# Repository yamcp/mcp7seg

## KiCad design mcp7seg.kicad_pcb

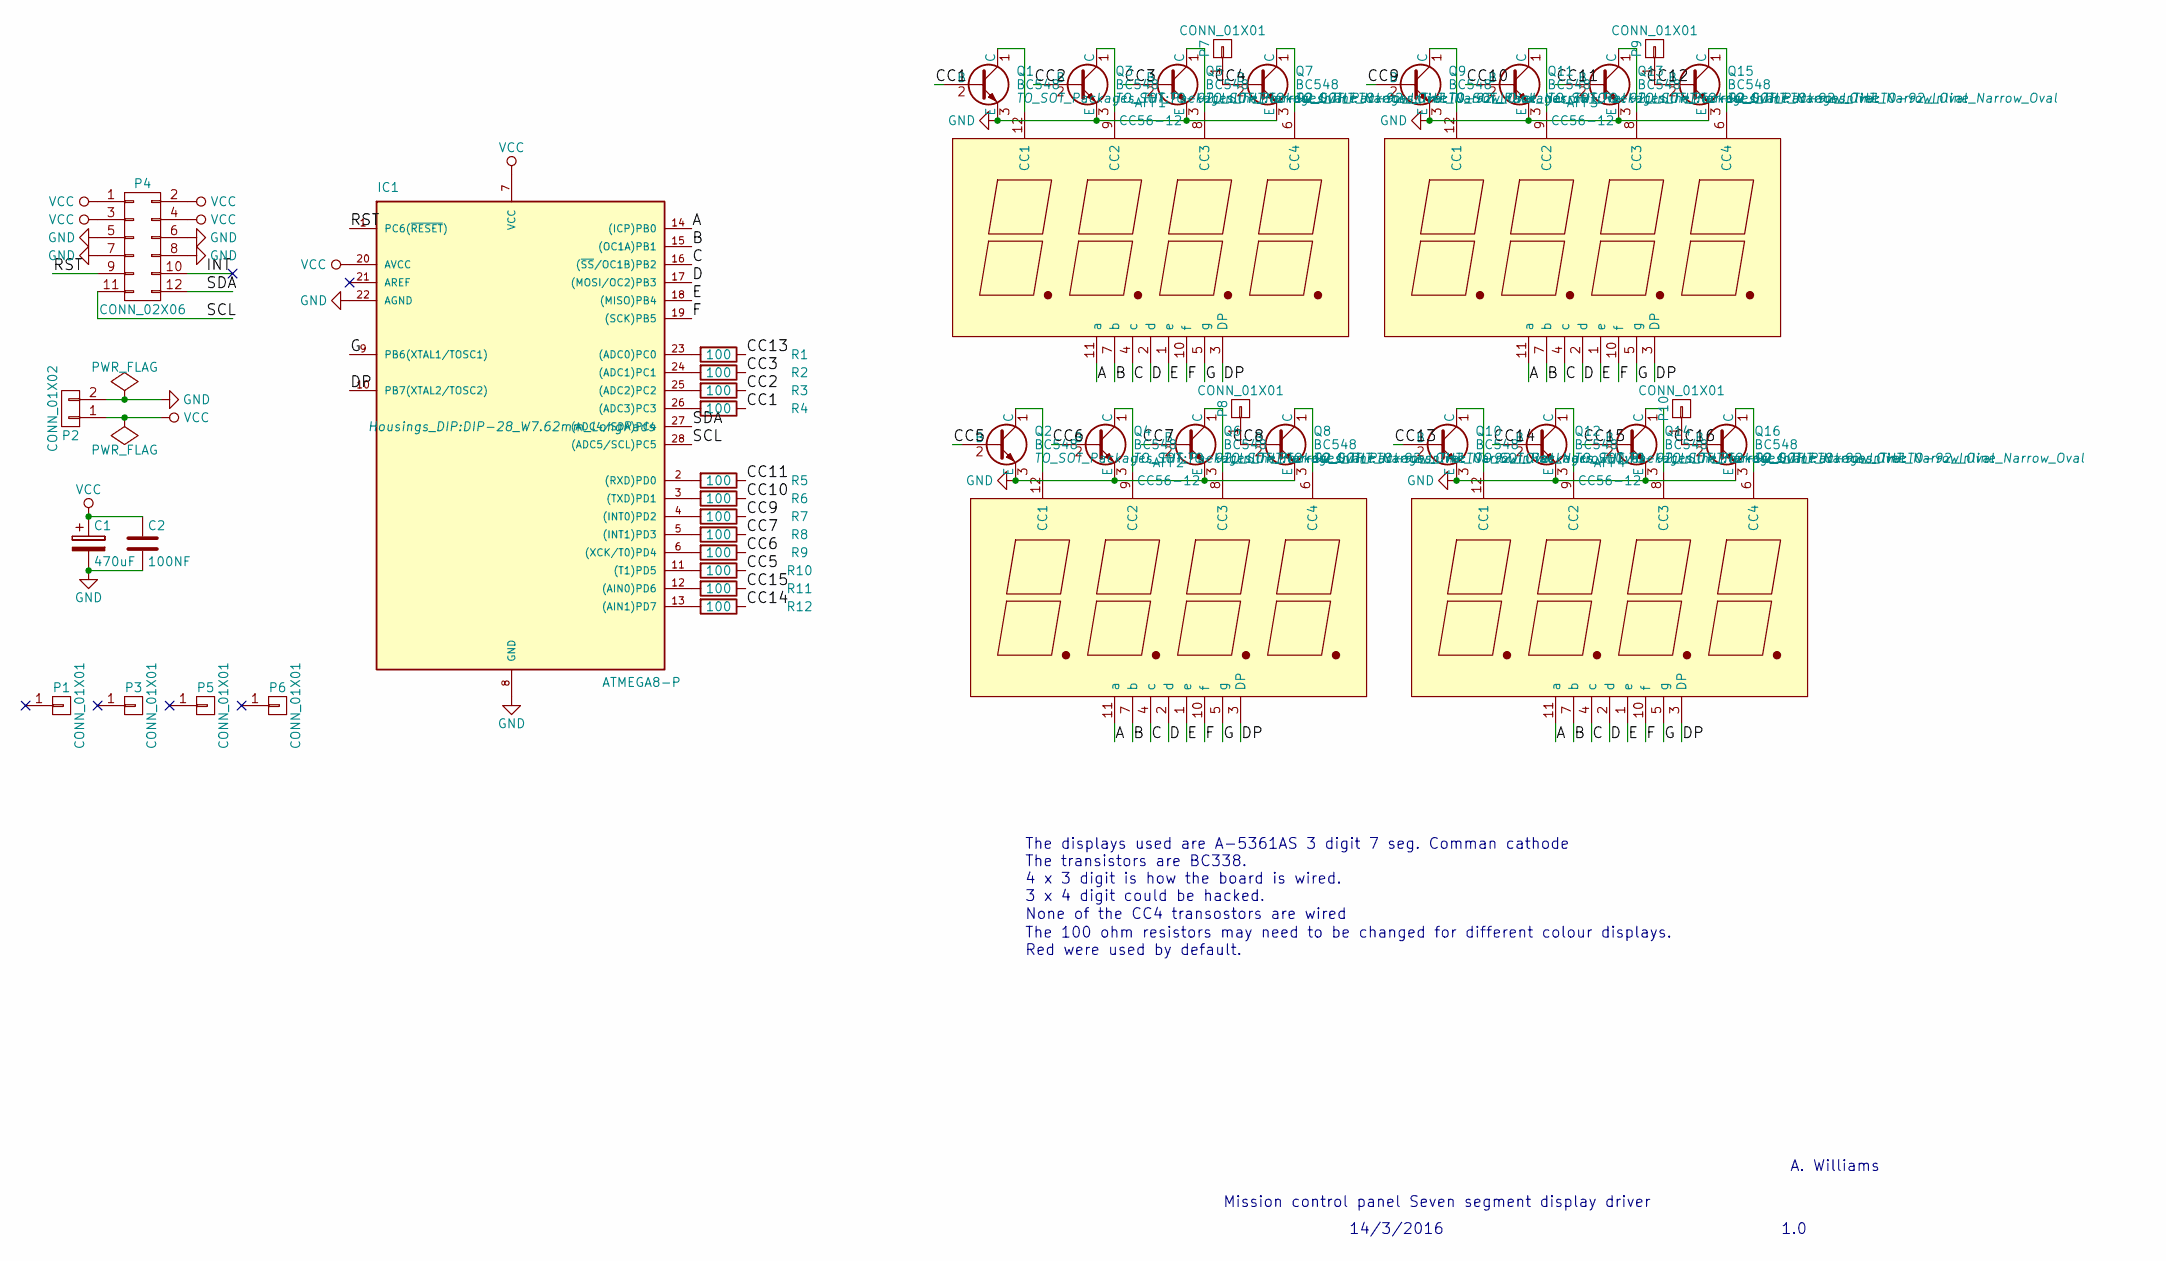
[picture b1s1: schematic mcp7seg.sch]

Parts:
AFF1, AFF2, AFF3, AFF4: CC56-12; Cx56-12
C1: 470uF; C_Radial_D8_L13_P3.8
C2: 100NF; C_Rect_L7_W2_P5
IC1: ATMEGA8-P; DIP-28_W7.62mm_LongPads
P1, P3, P5, P6: CONN_01X01; MountingHole_3.2mm_M3_Pad
P2: CONN_01X02; bornier2
P4: CONN_02X06; IDC_Header_Straight_12pins
P7, P8, P9, P10: CONN_01X01; 1pin
Q1, Q2, Q3, Q4, Q5, Q6, Q7, Q8, Q9, Q10, Q11, Q12, Q13, Q14, Q15, Q16: BC548; TO-92_Inline_Narrow_Oval
R1, R2, R3, R4, R5, R6, R7, R8, R9, R10, R11, R12: 100; Resistor_Horizontal_RM10mm

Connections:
/A: AFF1.11 (a), AFF2.11 (a), AFF3.11 (a), AFF4.11 (a), IC1.14 ((ICP)PB0)
/B: AFF1.7 (b), AFF2.7 (b), AFF3.7 (b), AFF4.7 (b), IC1.15 ((OC1A)PB1)
/C: AFF1.4 (c), AFF2.4 (c), AFF3.4 (c), AFF4.4 (c), IC1.16 ((~SS~/OC1B)PB2)
/CC1: Q1.2 (B), R4.1
/CC2: Q3.2 (B), R3.1
/CC3: Q5.2 (B), R2.1
/CC5: Q2.2 (B), R10.1
/CC6: Q4.2 (B), R9.1
/CC7: Q6.2 (B), R8.1
/CC9: Q9.2 (B), R7.1
/CC10: Q11.2 (B), R6.1
/CC11: Q13.2 (B), R5.1
/CC13: Q10.2 (B), R1.1
/CC14: Q12.2 (B), R12.1
/CC15: Q14.2 (B), R11.1
/D: AFF1.2 (d), AFF2.2 (d), AFF3.2 (d), AFF4.2 (d), IC1.17 ((MOSI/OC2)PB3)
/DP: AFF1.3 (DP), AFF2.3 (DP), AFF3.3 (DP), AFF4.3 (DP), IC1.10 (PB7(XTAL2/TOSC2))
/E: AFF1.1 (e), AFF2.1 (e), AFF3.1 (e), AFF4.1 (e), IC1.18 ((MISO)PB4)
/F: AFF1.10 (f), AFF2.10 (f), AFF3.10 (f), AFF4.10 (f), IC1.19 ((SCK)PB5)
/G: AFF1.5 (g), AFF2.5 (g), AFF3.5 (g), AFF4.5 (g), IC1.9 (PB6(XTAL1/TOSC1))
/INT: P4.10
/RST: IC1.1 (PC6(~RESET~)), P4.9
/SCL: IC1.28 ((ADC5/SCL)PC5), P4.11
/SDA: IC1.27 ((ADC4/SDA)PC4), P4.12
GND: C1.2, C2.2, IC1.8 (GND), IC1.22 (AGND), P2.2, P4.5, P4.6, P4.7, P4.8, Q1.3 (E), Q2.3 (E), Q3.3 (E), Q4.3 (E), Q5.3 (E), Q6.3 (E), Q7.3 (E), Q8.3 (E), Q9.3 (E), Q10.3 (E), Q11.3 (E), Q12.3 (E), Q13.3 (E), Q14.3 (E), Q15.3 (E), Q16.3 (E)
unnamed: AFF1.6 (CC4), Q7.1 (C)
unnamed: AFF1.8 (CC3), Q5.1 (C)
unnamed: AFF1.9 (CC2), Q3.1 (C)
unnamed: AFF1.12 (CC1), Q1.1 (C)
unnamed: AFF2.6 (CC4), Q8.1 (C)
unnamed: AFF2.8 (CC3), Q6.1 (C)
unnamed: AFF2.9 (CC2), Q4.1 (C)
unnamed: AFF2.12 (CC1), Q2.1 (C)
unnamed: AFF3.6 (CC4), Q15.1 (C)
unnamed: AFF3.8 (CC3), Q13.1 (C)
unnamed: AFF3.9 (CC2), Q11.1 (C)
unnamed: AFF3.12 (CC1), Q9.1 (C)
unnamed: AFF4.6 (CC4), Q16.1 (C)
unnamed: AFF4.8 (CC3), Q14.1 (C)
unnamed: AFF4.9 (CC2), Q12.1 (C)
unnamed: AFF4.12 (CC1), Q10.1 (C)
unnamed: IC1.2 ((RXD)PD0), R5.2
unnamed: IC1.3 ((TXD)PD1), R6.2
unnamed: IC1.4 ((INT0)PD2), R7.2
unnamed: IC1.5 ((INT1)PD3), R8.2
unnamed: IC1.6 ((XCK/T0)PD4), R9.2
unnamed: IC1.11 ((T1)PD5), R10.2
unnamed: IC1.12 ((AIN0)PD6), R11.2
unnamed: IC1.13 ((AIN1)PD7), R12.2
unnamed: IC1.23 ((ADC0)PC0), R1.2
unnamed: IC1.24 ((ADC1)PC1), R2.2
unnamed: IC1.25 ((ADC2)PC2), R3.2
unnamed: IC1.26 ((ADC3)PC3), R4.2
unnamed: P7.1, Q7.2 (B)
unnamed: P8.1, Q8.2 (B)
unnamed: P9.1, Q15.2 (B)
unnamed: P10.1, Q16.2 (B)
VCC: C1.1, C2.1, IC1.7 (VCC), IC1.20 (AVCC), P2.1, P4.1, P4.2, P4.3, P4.4

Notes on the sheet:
The displays used are A-5361AS 3 digit 7 seg. Comman cathode The transistors are BC338. 4 x 3 digit is how the board is wired. 3 x 4 digit could be hacked.
None of the CC4 transostors are wired
The 100 ohm resistors may need to be changed for different colour displays. Red were used by default.
Mission control panel Seven segment display driver
14/3/2016
1.0
A. Williams

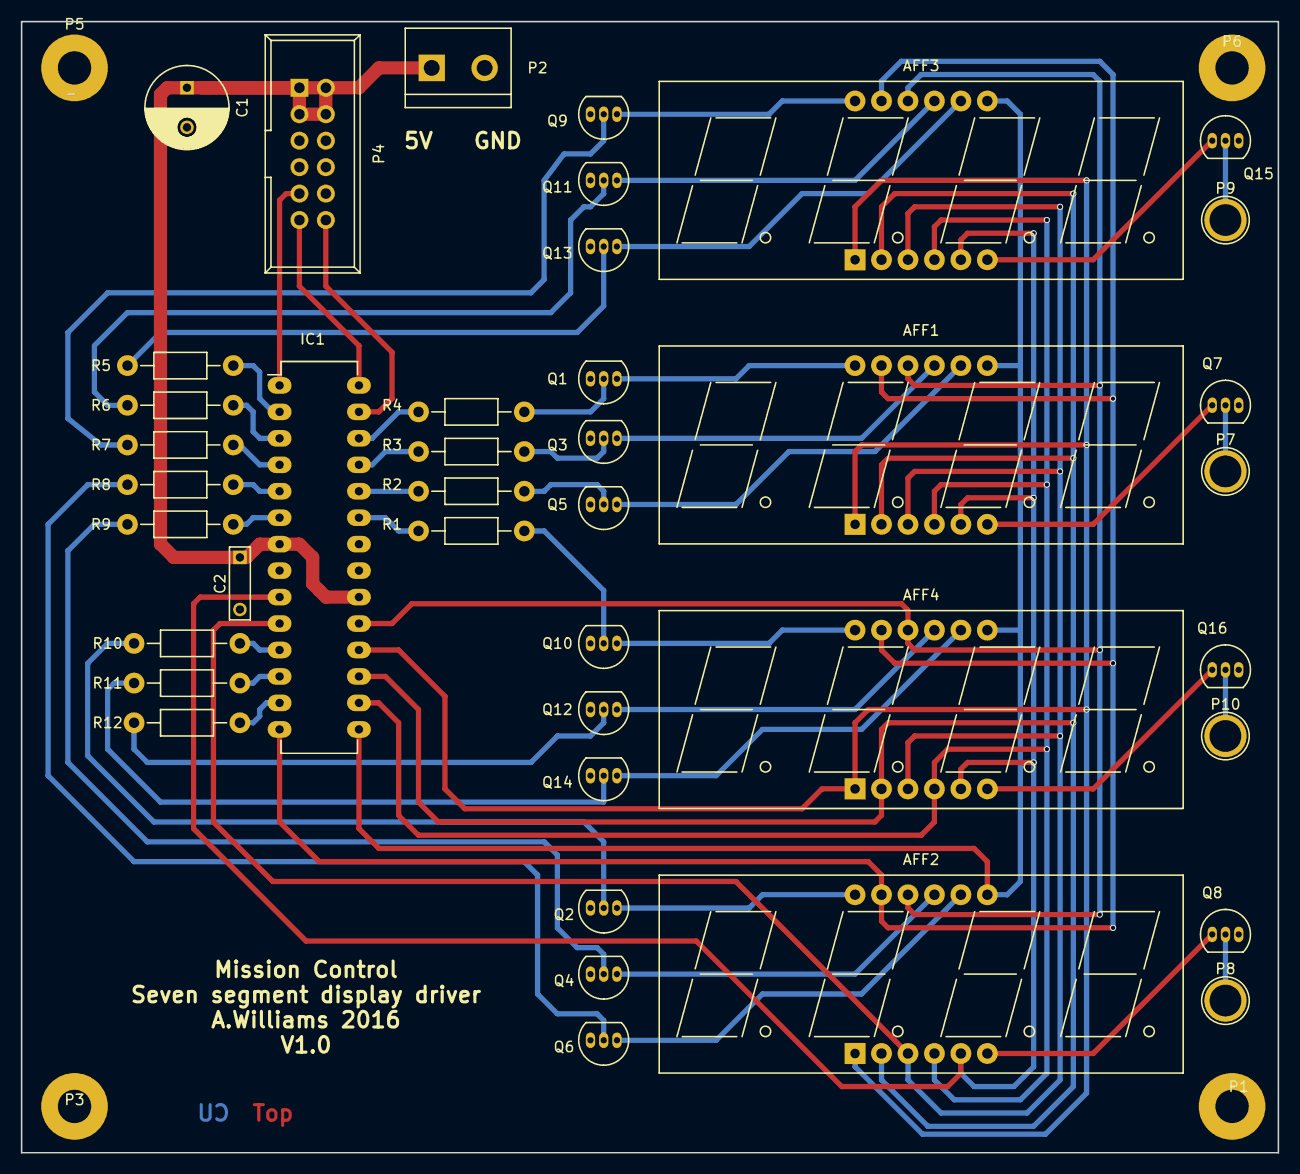
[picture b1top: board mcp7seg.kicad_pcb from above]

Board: 2 copper layers, 120.7 x 108.6 mm, 45 parts (0 on the bottom side), 57 nets.
